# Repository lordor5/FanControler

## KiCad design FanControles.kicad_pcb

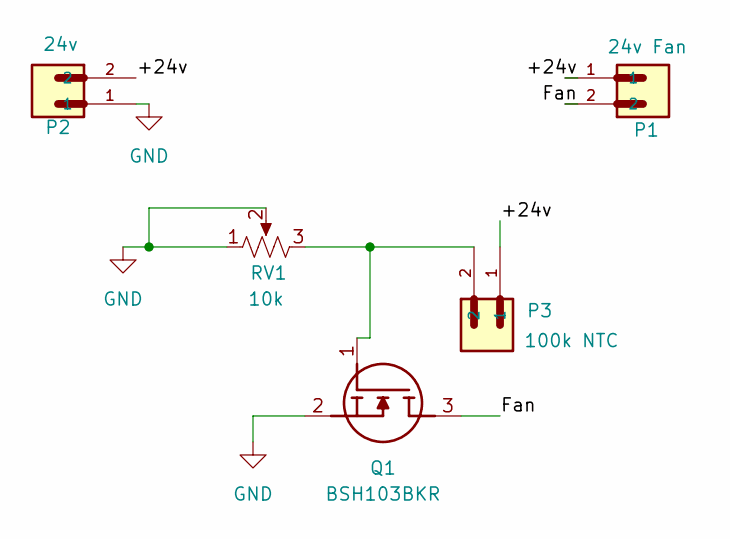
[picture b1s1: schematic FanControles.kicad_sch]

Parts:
P1: 24v Fan; JST_XH_S2B-XH-A_1x02_P2.50mm_Horizontal
P2: 24v; JST_XH_S2B-XH-A_1x02_P2.50mm_Horizontal
P3: 100k NTC; JST_XH_S2B-XH-A_1x02_P2.50mm_Horizontal
Q1: BSH103BKR; SOT95P230X110-3N; Mouser Part Number 771-BSH103BKR
RV1: 10k; Potentiometer_Bourns_3266W_Vertical; Manufacturer_Part_Number 3266 W-1-103_LF

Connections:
/+24v: P1.1, P2.2, P3.1
/Fan: P1.2, Q1.3 (D)
GND: P2.1, Q1.2 (S), RV1.1, RV1.2
unnamed: P3.2, Q1.1 (G), RV1.3

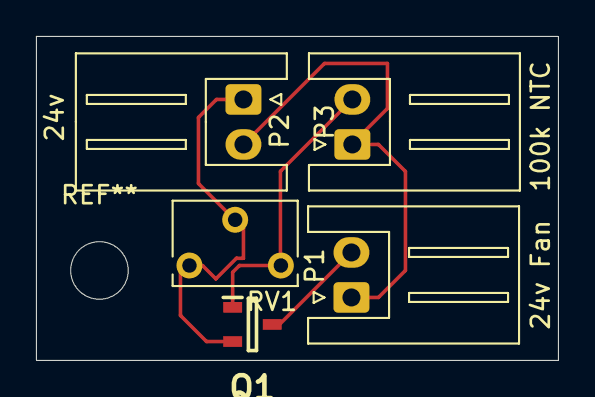
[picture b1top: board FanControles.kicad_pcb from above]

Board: 2 copper layers, 29.0 x 18.0 mm, 5 parts (0 on the bottom side), 4 nets.

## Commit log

2025-03-21 almost done
    TODO: change the potenciometer to a cheaper one
